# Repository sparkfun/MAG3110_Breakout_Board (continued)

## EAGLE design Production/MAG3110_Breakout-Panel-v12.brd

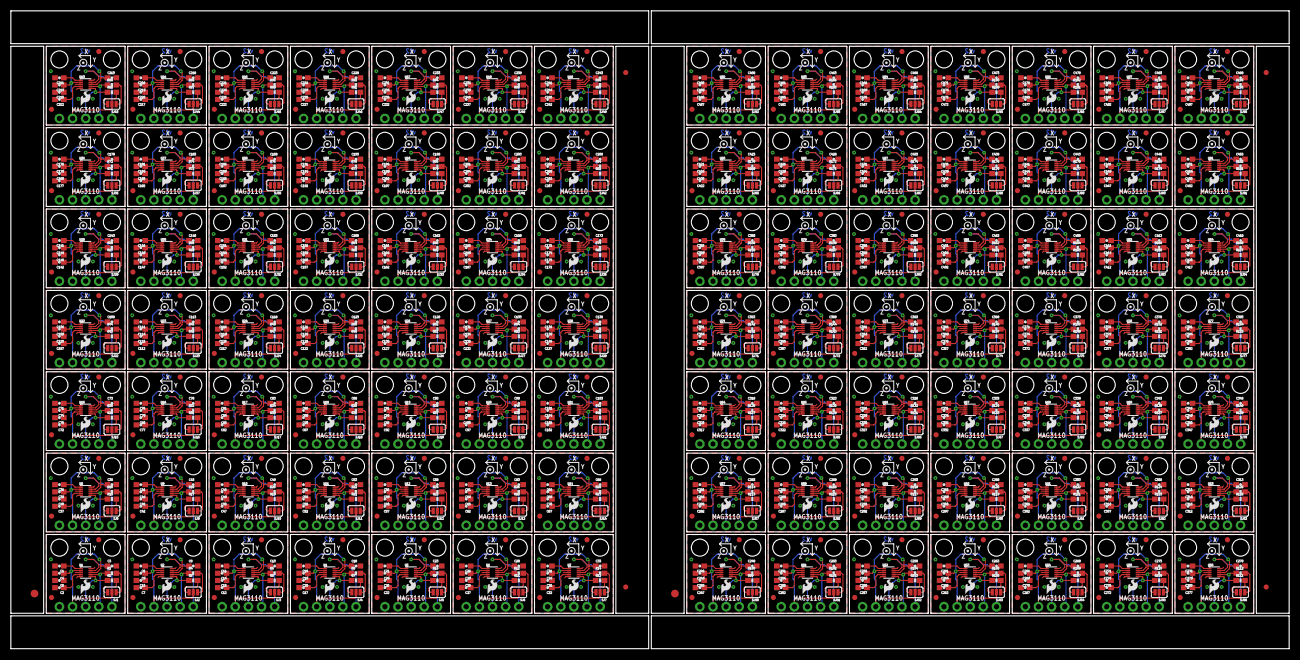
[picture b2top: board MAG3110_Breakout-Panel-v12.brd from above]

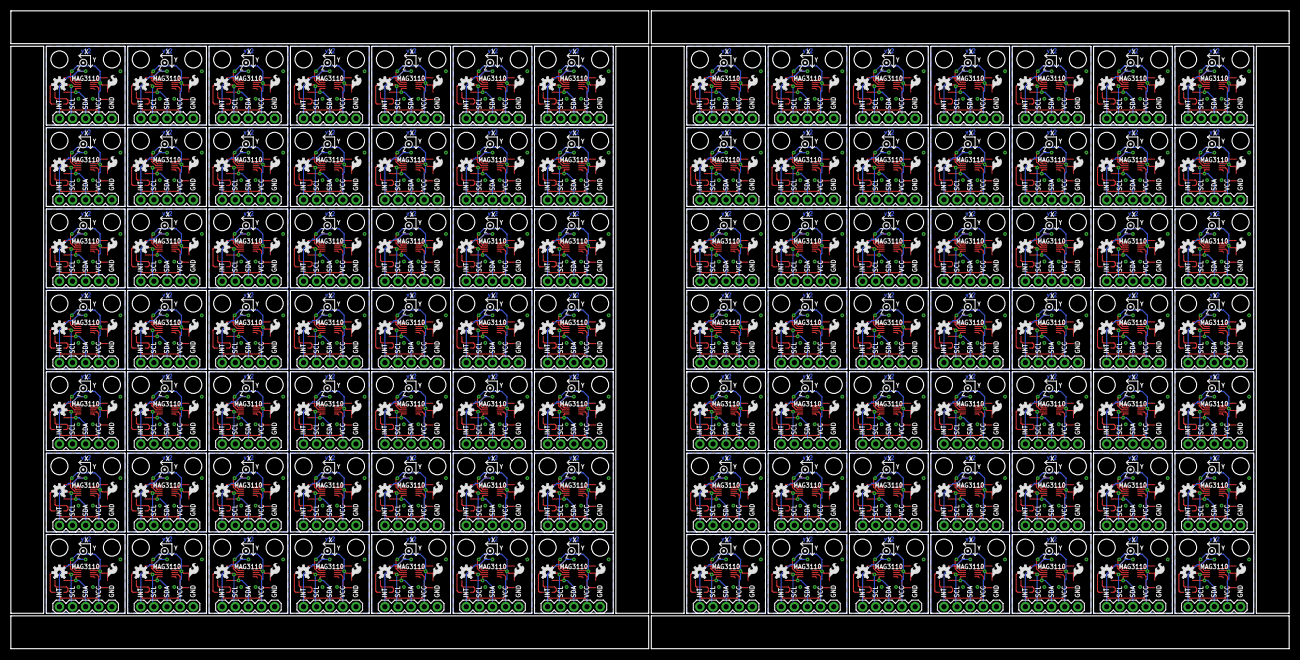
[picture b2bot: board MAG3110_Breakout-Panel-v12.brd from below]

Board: 2 copper layers, 247.4 x 123.4 mm, 1672 parts (294 on the bottom side), 882 nets.

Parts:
C1, C2, C3, C5, C6, C7, C8, C10, C11, C12, C13, C15, C16, C17, C18, C20, C21, C22, C23, C25, C26, C27, C28, C30, C31, C32, C33, C35, C36, C37, C38, C40, C41, C42, C43, C45, C46, C47, C48, C50, C51, C52, C53, C55, C56, C57, C58, C60, C61, C62, C63, C65, C66, C67, C68, C70, C71, C72, C73, C75, C76, C77, C78, C80, C81, C82, C83, C85, C86, C87, C88, C90, C91, C92, C93, C95, C96, C97, C98, C100, C101, C102, C103, C105, C106, C107, C108, C110, C111, C112, C113, C115, C116, C117, C118, C120, C121, C122, C123, C125, C126, C127, C128, C130, C131, C132, C133, C135, C136, C137, C138, C140, C141, C142, C143, C145, C146, C147, C148, C150, C151, C152, C153, C155, C156, C157, C158, C160, C161, C162, C163, C165, C166, C167, C168, C170, C171, C172, C173, C175, C176, C177, C178, C180, C181, C182, C183, C185, C186, C187, C188, C190, C191, C192, C193, C195, C196, C197, C198, C200, C201, C202, C203, C205, C206, C207, C208, C210, C211, C212, C213, C215, C216, C217, C218, C220, C221, C222, C223, C225, C226, C227, C228, C230, C231, C232, C233, C235, C236, C237, C238, C240, C241, C242, C243, C245, C246, C247, C248, C250, C251, C252, C253, C255, C256, C257, C258, C260, C261, C262, C263, C265, C266, C267, C268, C270, C271, C272, C273, C275, C276, C277, C278, C280, C281, C282, C283, C285, C286, C287, C288, C290, C291, C292, C293, C295, C296, C297, C298, C300, C301, C302, C303, C305, C306, C307, C308, C310, C311, C312, C313, C315, C316, C317, C318, C320, C321, C322, C323, C325, C326, C327, C328, C330, C331, C332, C333, C335, C336, C337, C338, C340, C341, C342, C343, C345, C346, C347, C348, C350, C351, C352, C353, C355, C356, C357, C358, C360, C361, C362, C363, C365, C366, C367, C368, C370, C371, C372, C373, C375, C376, C377, C378, C380, C381, C382, C383, C385, C386, C387, C388, C390, C391, C392, C393, C395, C396, C397, C398, C400, C401, C402, C403, C405, C406, C407, C408, C410, C411, C412, C413, C415, C416, C417, C418, C420, C421, C422, C423, C425, C426, C427, C428, C430, C431, C432, C433, C435, C436, C437, C438, C440, C441, C442, C443, C445, C446, C447, C448, C450, C451, C452, C453, C455, C456, C457, C458, C460, C461, C462, C463, C465, C466, C467, C468, C470, C471, C472, C473, C475, C476, C477, C478, C480, C481, C482, C483, C485, C486, C487, C488, C490: 0.1uF; 0603-CAP
C4, C9, C14, C19, C24, C29, C34, C39, C44, C49, C54, C59, C64, C69, C74, C79, C84, C89, C94, C99, C104, C109, C114, C119, C124, C129, C134, C139, C144, C149, C154, C159, C164, C169, C174, C179, C184, C189, C194, C199, C204, C209, C214, C219, C224, C229, C234, C239, C244, C249, C254, C259, C264, C269, C274, C279, C284, C289, C294, C299, C304, C309, C314, C319, C324, C329, C334, C339, C344, C349, C354, C359, C364, C369, C374, C379, C384, C389, C394, C399, C404, C409, C414, C419, C424, C429, C434, C439, C444, C449, C454, C459, C464, C469, C474, C479, C484, C489: 1uF; 0603-CAP
E$1, E$5: FIDUCIAL-1.5X3
E$2, E$3, E$4, E$6: FIDUCIAL-1X2
FID1, FID2, FID3, FID4, FID5, FID6, FID7, FID8, FID9, FID10, FID11, FID12, FID13, FID14, FID15, FID16, FID17, FID18, FID19, FID20, FID21, FID22, FID23, FID24, FID25, FID26, FID27, FID28, FID29, FID30, FID31, FID32, FID33, FID34, FID35, FID36, FID37, FID38, FID39, FID40, FID41, FID42, FID43, FID44, FID45, FID46, FID47, FID48, FID49, FID50, FID51, FID52, FID53, FID54, FID55, FID56, FID57, FID58, FID59, FID60, FID61, FID62, FID63, FID64, FID65, FID66, FID67, FID68, FID69, FID70, FID71, FID72, FID73, FID74, FID75, FID76, FID77, FID78, FID79, FID80, FID81, FID82, FID83, FID84, FID85, FID86, FID87, FID88, FID89, FID90, FID91, FID92, FID93, FID94, FID95, FID96, FID97, FID98, FID99, FID100, FID101, FID102, FID103, FID104, FID105, FID106, FID107, FID108, FID109, FID110, FID111, FID112, FID113, FID114, FID115, FID116, FID117, FID118, FID119, FID120, FID121, FID122, FID123, FID124, FID125, FID126, FID127, FID128, FID129, FID130, FID131, FID132, FID133, FID134, FID135, FID136, FID137, FID138, FID139, FID140, FID141, FID142, FID143, FID144, FID145, FID146, FID147, FID148, FID149, FID150, FID151, FID152, FID153, FID154, FID155, FID156, FID157, FID158, FID159, FID160, FID161, FID162, FID163, FID164, FID165, FID166, FID167, FID168, FID169, FID170, FID171, FID172, FID173, FID174, FID175, FID176, FID177, FID178, FID179, FID180, FID181, FID182, FID183, FID184, FID185, FID186, FID187, FID188, FID189, FID190, FID191, FID192, FID193, FID194, FID195, FID196: FIDUCIAL1X2; FIDUCIAL-1X2
JP1, JP5, JP11, JP16, JP21, JP26, JP31, JP36, JP41, JP46, JP51, JP56, JP61, JP66, JP71, JP76, JP81, JP86, JP91, JP96, JP101, JP106, JP111, JP116, JP121, JP126, JP131, JP136, JP141, JP146, JP151, JP156, JP161, JP166, JP171, JP176, JP181, JP186, JP191, JP196, JP201, JP206, JP211, JP216, JP221, JP226, JP231, JP236, JP241, JP246, JP251, JP256, JP261, JP266, JP271, JP276, JP281, JP286, JP291, JP296, JP301, JP306, JP311, JP316, JP321, JP326, JP331, JP336, JP341, JP346, JP351, JP356, JP361, JP366, JP371, JP376, JP381, JP386, JP391, JP396, JP401, JP406, JP411, JP416, JP421, JP426, JP431, JP436, JP441, JP446, JP451, JP456, JP461, JP466, JP471, JP476, JP481, JP486: breakout; 1X05
JP2, JP3, JP6, JP8, JP12, JP13, JP17, JP18, JP22, JP23, JP27, JP28, JP32, JP33, JP37, JP38, JP42, JP43, JP47, JP48, JP52, JP53, JP57, JP58, JP62, JP63, JP67, JP68, JP72, JP73, JP77, JP78, JP82, JP83, JP87, JP88, JP92, JP93, JP97, JP98, JP102, JP103, JP107, JP108, JP112, JP113, JP117, JP118, JP122, JP123, JP127, JP128, JP132, JP133, JP137, JP138, JP142, JP143, JP147, JP148, JP152, JP153, JP157, JP158, JP162, JP163, JP167, JP168, JP172, JP173, JP177, JP178, JP182, JP183, JP187, JP188, JP192, JP193, JP197, JP198, JP202, JP203, JP207, JP208, JP212, JP213, JP217, JP218, JP222, JP223, JP227, JP228, JP232, JP233, JP237, JP238, JP242, JP243, JP247, JP248, JP252, JP253, JP257, JP258, JP262, JP263, JP267, JP268, JP272, JP273, JP277, JP278, JP282, JP283, JP287, JP288, JP292, JP293, JP297, JP298, JP302, JP303, JP307, JP308, JP312, JP313, JP317, JP318, JP322, JP323, JP327, JP328, JP332, JP333, JP337, JP338, JP342, JP343, JP347, JP348, JP352, JP353, JP357, JP358, JP362, JP363, JP367, JP368, JP372, JP373, JP377, JP378, JP382, JP383, JP387, JP388, JP392, JP393, JP397, JP398, JP402, JP403, JP407, JP408, JP412, JP413, JP417, JP418, JP422, JP423, JP427, JP428, JP432, JP433, JP437, JP438, JP442, JP443, JP447, JP448, JP452, JP453, JP457, JP458, JP462, JP463, JP467, JP468, JP472, JP473, JP477, JP478, JP482, JP483, JP487, JP488: STAND-OFF
JP4, JP7, JP9, JP10, JP14, JP15, JP19, JP20, JP24, JP25, JP29, JP30, JP34, JP35, JP39, JP40, JP44, JP45, JP49, JP50, JP54, JP55, JP59, JP60, JP64, JP65, JP69, JP70, JP74, JP75, JP79, JP80, JP84, JP85, JP89, JP90, JP94, JP95, JP99, JP100, JP104, JP105, JP109, JP110, JP114, JP115, JP119, JP120, JP124, JP125, JP129, JP130, JP134, JP135, JP139, JP140, JP144, JP145, JP149, JP150, JP154, JP155, JP159, JP160, JP164, JP165, JP169, JP170, JP174, JP175, JP179, JP180, JP184, JP185, JP189, JP190, JP194, JP195, JP199, JP200, JP204, JP205, JP209, JP210, JP214, JP215, JP219, JP220, JP224, JP225, JP229, JP230, JP234, JP235, JP239, JP240, JP244, JP245, JP249, JP250, JP254, JP255, JP259, JP260, JP264, JP265, JP269, JP270, JP274, JP275, JP279, JP280, JP284, JP285, JP289, JP290, JP294, JP295, JP299, JP300, JP304, JP305, JP309, JP310, JP314, JP315, JP319, JP320, JP324, JP325, JP329, JP330, JP334, JP335, JP339, JP340, JP344, JP345, JP349, JP350, JP354, JP355, JP359, JP360, JP364, JP365, JP369, JP370, JP374, JP375, JP379, JP380, JP384, JP385, JP389, JP390, JP394, JP395, JP399, JP400, JP404, JP405, JP409, JP410, JP414, JP415, JP419, JP420, JP424, JP425, JP429, JP430, JP434, JP435, JP439, JP440, JP444, JP445, JP449, JP450, JP454, JP455, JP459, JP460, JP464, JP465, JP469, JP470, JP474, JP475, JP479, JP480, JP484, JP485, JP489, JP490: LOGO-SFESK; SFE-LOGO-FLAME
LOGO1, LOGO2, LOGO3, LOGO4, LOGO5, LOGO6, LOGO7, LOGO8, LOGO9, LOGO10, LOGO11, LOGO12, LOGO13, LOGO14, LOGO15, LOGO16, LOGO17, LOGO18, LOGO19, LOGO20, LOGO21, LOGO22, LOGO23, LOGO24, LOGO25, LOGO26, LOGO27, LOGO28, LOGO29, LOGO30, LOGO31, LOGO32, LOGO33, LOGO34, LOGO35, LOGO36, LOGO37, LOGO38, LOGO39, LOGO40, LOGO41, LOGO42, LOGO43, LOGO44, LOGO45, LOGO46, LOGO47, LOGO48, LOGO49, LOGO50, LOGO51, LOGO52, LOGO53, LOGO54, LOGO55, LOGO56, LOGO57, LOGO58, LOGO59, LOGO60, LOGO61, LOGO62, LOGO63, LOGO64, LOGO65, LOGO66, LOGO67, LOGO68, LOGO69, LOGO70, LOGO71, LOGO72, LOGO73, LOGO74, LOGO75, LOGO76, LOGO77, LOGO78, LOGO79, LOGO80, LOGO81, LOGO82, LOGO83, LOGO84, LOGO85, LOGO86, LOGO87, LOGO88, LOGO89, LOGO90, LOGO91, LOGO92, LOGO93, LOGO94, LOGO95, LOGO96, LOGO97, LOGO98: OSHW-LOGOS; OSHW-LOGO-S
R1, R2, R3, R4, R5, R6, R7, R8, R9, R10, R11, R12, R13, R14, R15, R16, R17, R18, R19, R20, R21, R22, R23, R24, R25, R26, R27, R28, R29, R30, R31, R32, R33, R34, R35, R36, R37, R38, R39, R40, R41, R42, R43, R44, R45, R46, R47, R48, R49, R50, R51, R52, R53, R54, R55, R56, R57, R58, R59, R60, R61, R62, R63, R64, R65, R66, R67, R68, R69, R70, R71, R72, R73, R74, R75, R76, R77, R78, R79, R80, R81, R82, R83, R84, R85, R86, R87, R88, R89, R90, R91, R92, R93, R94, R95, R96, R97, R98, R99, R100, R101, R102, R103, R104, R105, R106, R107, R108, R109, R110, R111, R112, R113, R114, R115, R116, R117, R118, R119, R120, R121, R122, R123, R124, R125, R126, R127, R128, R129, R130, R131, R132, R133, R134, R135, R136, R137, R138, R139, R140, R141, R142, R143, R144, R145, R146, R147, R148, R149, R150, R151, R152, R153, R154, R155, R156, R157, R158, R159, R160, R161, R162, R163, R164, R165, R166, R167, R168, R169, R170, R171, R172, R173, R174, R175, R176, R177, R178, R179, R180, R181, R182, R183, R184, R185, R186, R187, R188, R189, R190, R191, R192, R193, R194, R195, R196: 4.7k; 0603-RES
SJ1, SJ2, SJ3, SJ4, SJ5, SJ6, SJ7, SJ8, SJ9, SJ10, SJ11, SJ12, SJ13, SJ14, SJ15, SJ16, SJ17, SJ18, SJ19, SJ20, SJ21, SJ22, SJ23, SJ24, SJ25, SJ26, SJ27, SJ28, SJ29, SJ30, SJ31, SJ32, SJ33, SJ34, SJ35, SJ36, SJ37, SJ38, SJ39, SJ40, SJ41, SJ42, SJ43, SJ44, SJ45, SJ46, SJ47, SJ48, SJ49, SJ50, SJ51, SJ52, SJ53, SJ54, SJ55, SJ56, SJ57, SJ58, SJ59, SJ60, SJ61, SJ62, SJ63, SJ64, SJ65, SJ66, SJ67, SJ68, SJ69, SJ70, SJ71, SJ72, SJ73, SJ74, SJ75, SJ76, SJ77, SJ78, SJ79, SJ80, SJ81, SJ82, SJ83, SJ84, SJ85, SJ86, SJ87, SJ88, SJ89, SJ90, SJ91, SJ92, SJ93, SJ94, SJ95, SJ96, SJ97, SJ98: SJ_3_PASTE1&2&3
U1, U2, U3, U4, U5, U6, U7, U8, U9, U10, U11, U12, U13, U14, U15, U16, U17, U18, U19, U20, U21, U22, U23, U24, U25, U26, U27, U28, U29, U30, U31, U32, U33, U34, U35, U36, U37, U38, U39, U40, U41, U42, U43, U44, U45, U46, U47, U48, U49, U50, U51, U52, U53, U54, U55, U56, U57, U58, U59, U60, U61, U62, U63, U64, U65, U66, U67, U68, U69, U70, U71, U72, U73, U74, U75, U76, U77, U78, U79, U80, U81, U82, U83, U84, U85, U86, U87, U88, U89, U90, U91, U92, U93, U94, U95, U96, U97, U98: MAG31101:1; DFN-10-W

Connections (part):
GND: C1.2, C2.2, C3.2, C4.2, C5.2, JP1.1, U1.5, U1.10
GND1: C6.2, C7.2, C8.2, C9.2, C10.2, JP5.1, U2.5, U2.10
GND2: C11.2, C12.2, C13.2, C14.2, C15.2, JP11.1, U3.5, U3.10
GND3: C16.2, C17.2, C18.2, C19.2, C20.2, JP16.1, U4.5, U4.10
GND4: C21.2, C22.2, C23.2, C24.2, C25.2, JP21.1, U5.5, U5.10
GND5: C26.2, C27.2, C28.2, C29.2, C30.2, JP26.1, U6.5, U6.10
GND6: C31.2, C32.2, C33.2, C34.2, C35.2, JP31.1, U7.5, U7.10
GND7: C36.2, C37.2, C38.2, C39.2, C40.2, JP36.1, U8.5, U8.10
GND8: C41.2, C42.2, C43.2, C44.2, C45.2, JP41.1, U9.5, U9.10
GND9: C46.2, C47.2, C48.2, C49.2, C50.2, JP46.1, U10.5, U10.10
GND10: C51.2, C52.2, C53.2, C54.2, C55.2, JP51.1, U11.5, U11.10
GND11: C56.2, C57.2, C58.2, C59.2, C60.2, JP56.1, U12.5, U12.10
GND12: C61.2, C62.2, C63.2, C64.2, C65.2, JP61.1, U13.5, U13.10
GND13: C66.2, C67.2, C68.2, C69.2, C70.2, JP66.1, U14.5, U14.10
GND14: C71.2, C72.2, C73.2, C74.2, C75.2, JP71.1, U15.5, U15.10
GND15: C76.2, C77.2, C78.2, C79.2, C80.2, JP76.1, U16.5, U16.10
GND16: C81.2, C82.2, C83.2, C84.2, C85.2, JP81.1, U17.5, U17.10
GND17: C86.2, C87.2, C88.2, C89.2, C90.2, JP86.1, U18.5, U18.10
GND18: C91.2, C92.2, C93.2, C94.2, C95.2, JP91.1, U19.5, U19.10
GND19: C96.2, C97.2, C98.2, C99.2, C100.2, JP96.1, U20.5, U20.10
GND20: C101.2, C102.2, C103.2, C104.2, C105.2, JP101.1, U21.5, U21.10
GND21: C106.2, C107.2, C108.2, C109.2, C110.2, JP106.1, U22.5, U22.10
GND22: C111.2, C112.2, C113.2, C114.2, C115.2, JP111.1, U23.5, U23.10
GND23: C116.2, C117.2, C118.2, C119.2, C120.2, JP116.1, U24.5, U24.10
GND24: C121.2, C122.2, C123.2, C124.2, C125.2, JP121.1, U25.5, U25.10
GND25: C126.2, C127.2, C128.2, C129.2, C130.2, JP126.1, U26.5, U26.10
GND26: C131.2, C132.2, C133.2, C134.2, C135.2, JP131.1, U27.5, U27.10
GND27: C136.2, C137.2, C138.2, C139.2, C140.2, JP136.1, U28.5, U28.10
GND28: C141.2, C142.2, C143.2, C144.2, C145.2, JP141.1, U29.5, U29.10
GND29: C146.2, C147.2, C148.2, C149.2, C150.2, JP146.1, U30.5, U30.10
GND30: C151.2, C152.2, C153.2, C154.2, C155.2, JP151.1, U31.5, U31.10
GND31: C156.2, C157.2, C158.2, C159.2, C160.2, JP156.1, U32.5, U32.10
GND32: C161.2, C162.2, C163.2, C164.2, C165.2, JP161.1, U33.5, U33.10
GND33: C166.2, C167.2, C168.2, C169.2, C170.2, JP166.1, U34.5, U34.10
GND34: C171.2, C172.2, C173.2, C174.2, C175.2, JP171.1, U35.5, U35.10
GND35: C176.2, C177.2, C178.2, C179.2, C180.2, JP176.1, U36.5, U36.10
GND36: C181.2, C182.2, C183.2, C184.2, C185.2, JP181.1, U37.5, U37.10
GND37: C186.2, C187.2, C188.2, C189.2, C190.2, JP186.1, U38.5, U38.10
GND38: C191.2, C192.2, C193.2, C194.2, C195.2, JP191.1, U39.5, U39.10
GND39: C196.2, C197.2, C198.2, C199.2, C200.2, JP196.1, U40.5, U40.10
GND40: C201.2, C202.2, C203.2, C204.2, C205.2, JP201.1, U41.5, U41.10
GND41: C206.2, C207.2, C208.2, C209.2, C210.2, JP206.1, U42.5, U42.10
GND42: C211.2, C212.2, C213.2, C214.2, C215.2, JP211.1, U43.5, U43.10
GND43: C216.2, C217.2, C218.2, C219.2, C220.2, JP216.1, U44.5, U44.10
GND44: C221.2, C222.2, C223.2, C224.2, C225.2, JP221.1, U45.5, U45.10
GND45: C226.2, C227.2, C228.2, C229.2, C230.2, JP226.1, U46.5, U46.10
GND46: C231.2, C232.2, C233.2, C234.2, C235.2, JP231.1, U47.5, U47.10
GND47: C236.2, C237.2, C238.2, C239.2, C240.2, JP236.1, U48.5, U48.10
GND48: C241.2, C242.2, C243.2, C244.2, C245.2, JP241.1, U49.5, U49.10
GND49: C246.2, C247.2, C248.2, C249.2, C250.2, JP246.1, U50.5, U50.10
GND50: C251.2, C252.2, C253.2, C254.2, C255.2, JP251.1, U51.5, U51.10
GND51: C256.2, C257.2, C258.2, C259.2, C260.2, JP256.1, U52.5, U52.10
GND52: C261.2, C262.2, C263.2, C264.2, C265.2, JP261.1, U53.5, U53.10
GND53: C266.2, C267.2, C268.2, C269.2, C270.2, JP266.1, U54.5, U54.10
GND54: C271.2, C272.2, C273.2, C274.2, C275.2, JP271.1, U55.5, U55.10
GND55: C276.2, C277.2, C278.2, C279.2, C280.2, JP276.1, U56.5, U56.10
GND56: C281.2, C282.2, C283.2, C284.2, C285.2, JP281.1, U57.5, U57.10
GND57: C286.2, C287.2, C288.2, C289.2, C290.2, JP286.1, U58.5, U58.10
GND58: C291.2, C292.2, C293.2, C294.2, C295.2, JP291.1, U59.5, U59.10
GND59: C296.2, C297.2, C298.2, C299.2, C300.2, JP296.1, U60.5, U60.10
GND60: C301.2, C302.2, C303.2, C304.2, C305.2, JP301.1, U61.5, U61.10
GND61: C306.2, C307.2, C308.2, C309.2, C310.2, JP306.1, U62.5, U62.10
GND62: C311.2, C312.2, C313.2, C314.2, C315.2, JP311.1, U63.5, U63.10
GND63: C316.2, C317.2, C318.2, C319.2, C320.2, JP316.1, U64.5, U64.10
GND64: C321.2, C322.2, C323.2, C324.2, C325.2, JP321.1, U65.5, U65.10
GND65: C326.2, C327.2, C328.2, C329.2, C330.2, JP326.1, U66.5, U66.10
GND66: C331.2, C332.2, C333.2, C334.2, C335.2, JP331.1, U67.5, U67.10
GND67: C336.2, C337.2, C338.2, C339.2, C340.2, JP336.1, U68.5, U68.10
GND68: C341.2, C342.2, C343.2, C344.2, C345.2, JP341.1, U69.5, U69.10
GND69: C346.2, C347.2, C348.2, C349.2, C350.2, JP346.1, U70.5, U70.10
GND70: C351.2, C352.2, C353.2, C354.2, C355.2, JP351.1, U71.5, U71.10
GND71: C356.2, C357.2, C358.2, C359.2, C360.2, JP356.1, U72.5, U72.10
GND72: C361.2, C362.2, C363.2, C364.2, C365.2, JP361.1, U73.5, U73.10
GND73: C366.2, C367.2, C368.2, C369.2, C370.2, JP366.1, U74.5, U74.10
GND74: C371.2, C372.2, C373.2, C374.2, C375.2, JP371.1, U75.5, U75.10
GND75: C376.2, C377.2, C378.2, C379.2, C380.2, JP376.1, U76.5, U76.10
GND76: C381.2, C382.2, C383.2, C384.2, C385.2, JP381.1, U77.5, U77.10
GND77: C386.2, C387.2, C388.2, C389.2, C390.2, JP386.1, U78.5, U78.10
GND78: C391.2, C392.2, C393.2, C394.2, C395.2, JP391.1, U79.5, U79.10
GND79: C396.2, C397.2, C398.2, C399.2, C400.2, JP396.1, U80.5, U80.10
GND80: C401.2, C402.2, C403.2, C404.2, C405.2, JP401.1, U81.5, U81.10
GND81: C406.2, C407.2, C408.2, C409.2, C410.2, JP406.1, U82.5, U82.10
GND82: C411.2, C412.2, C413.2, C414.2, C415.2, JP411.1, U83.5, U83.10
GND83: C416.2, C417.2, C418.2, C419.2, C420.2, JP416.1, U84.5, U84.10
GND84: C421.2, C422.2, C423.2, C424.2, C425.2, JP421.1, U85.5, U85.10
GND85: C426.2, C427.2, C428.2, C429.2, C430.2, JP426.1, U86.5, U86.10
GND86: C431.2, C432.2, C433.2, C434.2, C435.2, JP431.1, U87.5, U87.10
GND87: C436.2, C437.2, C438.2, C439.2, C440.2, JP436.1, U88.5, U88.10
GND88: C441.2, C442.2, C443.2, C444.2, C445.2, JP441.1, U89.5, U89.10
GND89: C446.2, C447.2, C448.2, C449.2, C450.2, JP446.1, U90.5, U90.10
GND90: C451.2, C452.2, C453.2, C454.2, C455.2, JP451.1, U91.5, U91.10
GND91: C456.2, C457.2, C458.2, C459.2, C460.2, JP456.1, U92.5, U92.10
GND92: C461.2, C462.2, C463.2, C464.2, C465.2, JP461.1, U93.5, U93.10
GND93: C466.2, C467.2, C468.2, C469.2, C470.2, JP466.1, U94.5, U94.10
GND94: C471.2, C472.2, C473.2, C474.2, C475.2, JP471.1, U95.5, U95.10
GND95: C476.2, C477.2, C478.2, C479.2, C480.2, JP476.1, U96.5, U96.10
GND96: C481.2, C482.2, C483.2, C484.2, C485.2, JP481.1, U97.5, U97.10
GND97: C486.2, C487.2, C488.2, C489.2, C490.2, JP486.1, U98.5, U98.10
INT: JP1.5, U1.9
INT1: JP5.5, U2.9
INT2: JP11.5, U3.9
INT3: JP16.5, U4.9
INT4: JP21.5, U5.9
INT5: JP26.5, U6.9
INT6: JP31.5, U7.9
INT7: JP36.5, U8.9
INT8: JP41.5, U9.9
INT9: JP46.5, U10.9
INT10: JP51.5, U11.9
INT11: JP56.5, U12.9
INT12: JP61.5, U13.9
INT13: JP66.5, U14.9
INT14: JP71.5, U15.9
INT15: JP76.5, U16.9
INT16: JP81.5, U17.9
INT17: JP86.5, U18.9
INT18: JP91.5, U19.9
INT19: JP96.5, U20.9
INT20: JP101.5, U21.9
INT21: JP106.5, U22.9
INT22: JP111.5, U23.9
INT23: JP116.5, U24.9
INT24: JP121.5, U25.9
INT25: JP126.5, U26.9
INT26: JP131.5, U27.9
INT27: JP136.5, U28.9
INT28: JP141.5, U29.9
INT29: JP146.5, U30.9
INT30: JP151.5, U31.9
INT31: JP156.5, U32.9
INT32: JP161.5, U33.9
INT33: JP166.5, U34.9
INT34: JP171.5, U35.9
INT35: JP176.5, U36.9
INT36: JP181.5, U37.9
INT37: JP186.5, U38.9
INT38: JP191.5, U39.9
INT39: JP196.5, U40.9
INT40: JP201.5, U41.9
INT41: JP206.5, U42.9
INT42: JP211.5, U43.9
INT43: JP216.5, U44.9
INT44: JP221.5, U45.9
INT45: JP226.5, U46.9
INT46: JP231.5, U47.9
INT47: JP236.5, U48.9
INT48: JP241.5, U49.9
INT49: JP246.5, U50.9
INT50: JP251.5, U51.9
INT51: JP256.5, U52.9
INT52: JP261.5, U53.9
INT53: JP266.5, U54.9
INT54: JP271.5, U55.9
INT55: JP276.5, U56.9
INT56: JP281.5, U57.9
INT57: JP286.5, U58.9
INT58: JP291.5, U59.9
INT59: JP296.5, U60.9
INT60: JP301.5, U61.9
INT61: JP306.5, U62.9
INT62: JP311.5, U63.9
INT63: JP316.5, U64.9
INT64: JP321.5, U65.9
INT65: JP326.5, U66.9
INT66: JP331.5, U67.9
INT67: JP336.5, U68.9
INT68: JP341.5, U69.9
INT69: JP346.5, U70.9
INT70: JP351.5, U71.9
INT71: JP356.5, U72.9
INT72: JP361.5, U73.9
INT73: JP366.5, U74.9
INT74: JP371.5, U75.9
INT75: JP376.5, U76.9
INT76: JP381.5, U77.9
INT77: JP386.5, U78.9
INT78: JP391.5, U79.9
INT79: JP396.5, U80.9
INT80: JP401.5, U81.9
INT81: JP406.5, U82.9
INT82: JP411.5, U83.9
INT83: JP416.5, U84.9
INT84: JP421.5, U85.9
INT85: JP426.5, U86.9
INT86: JP431.5, U87.9
INT87: JP436.5, U88.9
INT88: JP441.5, U89.9
INT89: JP446.5, U90.9
INT90: JP451.5, U91.9
INT91: JP456.5, U92.9
INT92: JP461.5, U93.9
INT93: JP466.5, U94.9
INT94: JP471.5, U95.9
INT95: JP476.5, U96.9
INT96: JP481.5, U97.9
INT97: JP486.5, U98.9
unnamed: C2.1, U1.4
unnamed: C1.1, U1.1
unnamed: R2.2, SJ1.1
unnamed: R1.2, SJ1.3
unnamed: C7.1, U2.4
unnamed: C6.1, U2.1
unnamed: R4.2, SJ2.1
unnamed: R3.2, SJ2.3
unnamed: C12.1, U3.4
unnamed: C11.1, U3.1
unnamed: R6.2, SJ3.1
unnamed: R5.2, SJ3.3
unnamed: C17.1, U4.4
unnamed: C16.1, U4.1
unnamed: R8.2, SJ4.1
unnamed: R7.2, SJ4.3
unnamed: C22.1, U5.4
unnamed: C21.1, U5.1
unnamed: R10.2, SJ5.1
unnamed: R9.2, SJ5.3
unnamed: C27.1, U6.4
unnamed: C26.1, U6.1
unnamed: R12.2, SJ6.1
unnamed: R11.2, SJ6.3
unnamed: C32.1, U7.4
unnamed: C31.1, U7.1
unnamed: R14.2, SJ7.1
unnamed: R13.2, SJ7.3
unnamed: C37.1, U8.4
unnamed: C36.1, U8.1
unnamed: R16.2, SJ8.1
unnamed: R15.2, SJ8.3
unnamed: C42.1, U9.4
unnamed: C41.1, U9.1
unnamed: R18.2, SJ9.1
unnamed: R17.2, SJ9.3
unnamed: C47.1, U10.4
unnamed: C46.1, U10.1
unnamed: R20.2, SJ10.1
unnamed: R19.2, SJ10.3
unnamed: C52.1, U11.4
unnamed: C51.1, U11.1
unnamed: R22.2, SJ11.1
unnamed: R21.2, SJ11.3
unnamed: C57.1, U12.4
unnamed: C56.1, U12.1
unnamed: R24.2, SJ12.1
unnamed: R23.2, SJ12.3
unnamed: C62.1, U13.4
unnamed: C61.1, U13.1
unnamed: R26.2, SJ13.1
unnamed: R25.2, SJ13.3
unnamed: C67.1, U14.4
unnamed: C66.1, U14.1
unnamed: R28.2, SJ14.1
unnamed: R27.2, SJ14.3
unnamed: C72.1, U15.4
unnamed: C71.1, U15.1
unnamed: R30.2, SJ15.1
unnamed: R29.2, SJ15.3
unnamed: C77.1, U16.4
unnamed: C76.1, U16.1
unnamed: R32.2, SJ16.1
unnamed: R31.2, SJ16.3
unnamed: C82.1, U17.4
unnamed: C81.1, U17.1
unnamed: R34.2, SJ17.1
unnamed: R33.2, SJ17.3
unnamed: C87.1, U18.4
unnamed: C86.1, U18.1
unnamed: R36.2, SJ18.1
unnamed: R35.2, SJ18.3
unnamed: C92.1, U19.4
unnamed: C91.1, U19.1
unnamed: R38.2, SJ19.1
unnamed: R37.2, SJ19.3
unnamed: C97.1, U20.4
unnamed: C96.1, U20.1
unnamed: R40.2, SJ20.1
unnamed: R39.2, SJ20.3
unnamed: C102.1, U21.4
unnamed: C101.1, U21.1
unnamed: R42.2, SJ21.1
unnamed: R41.2, SJ21.3
unnamed: C107.1, U22.4
unnamed: C106.1, U22.1
unnamed: R44.2, SJ22.1
unnamed: R43.2, SJ22.3
unnamed: C112.1, U23.4
unnamed: C111.1, U23.1
unnamed: R46.2, SJ23.1
unnamed: R45.2, SJ23.3
unnamed: C117.1, U24.4
unnamed: C116.1, U24.1
unnamed: R48.2, SJ24.1
unnamed: R47.2, SJ24.3
unnamed: C122.1, U25.4
unnamed: C121.1, U25.1
unnamed: R50.2, SJ25.1
unnamed: R49.2, SJ25.3
unnamed: C127.1, U26.4
unnamed: C126.1, U26.1
unnamed: R52.2, SJ26.1
unnamed: R51.2, SJ26.3
unnamed: C132.1, U27.4
unnamed: C131.1, U27.1
unnamed: R54.2, SJ27.1
unnamed: R53.2, SJ27.3
unnamed: C137.1, U28.4
unnamed: C136.1, U28.1
unnamed: R56.2, SJ28.1
unnamed: R55.2, SJ28.3
unnamed: C142.1, U29.4
unnamed: C141.1, U29.1
unnamed: R58.2, SJ29.1
unnamed: R57.2, SJ29.3
unnamed: C147.1, U30.4
unnamed: C146.1, U30.1
unnamed: R60.2, SJ30.1
unnamed: R59.2, SJ30.3
unnamed: C152.1, U31.4
unnamed: C151.1, U31.1
unnamed: R62.2, SJ31.1
unnamed: R61.2, SJ31.3
unnamed: C157.1, U32.4
unnamed: C156.1, U32.1
unnamed: R64.2, SJ32.1
unnamed: R63.2, SJ32.3
unnamed: C162.1, U33.4
unnamed: C161.1, U33.1
unnamed: R66.2, SJ33.1
unnamed: R65.2, SJ33.3
unnamed: C167.1, U34.4
unnamed: C166.1, U34.1
unnamed: R68.2, SJ34.1
unnamed: R67.2, SJ34.3
unnamed: C172.1, U35.4
unnamed: C171.1, U35.1
unnamed: R70.2, SJ35.1
unnamed: R69.2, SJ35.3
unnamed: C177.1, U36.4
unnamed: C176.1, U36.1
unnamed: R72.2, SJ36.1
unnamed: R71.2, SJ36.3
unnamed: C182.1, U37.4
unnamed: C181.1, U37.1
unnamed: R74.2, SJ37.1
unnamed: R73.2, SJ37.3
unnamed: C187.1, U38.4
unnamed: C186.1, U38.1
unnamed: R76.2, SJ38.1
unnamed: R75.2, SJ38.3
unnamed: C192.1, U39.4
unnamed: C191.1, U39.1
unnamed: R78.2, SJ39.1
unnamed: R77.2, SJ39.3
unnamed: C197.1, U40.4
unnamed: C196.1, U40.1
unnamed: R80.2, SJ40.1
unnamed: R79.2, SJ40.3
unnamed: C202.1, U41.4
unnamed: C201.1, U41.1
unnamed: R82.2, SJ41.1
unnamed: R81.2, SJ41.3
unnamed: C207.1, U42.4
unnamed: C206.1, U42.1
unnamed: R84.2, SJ42.1
unnamed: R83.2, SJ42.3
unnamed: C212.1, U43.4
unnamed: C211.1, U43.1
unnamed: R86.2, SJ43.1
unnamed: R85.2, SJ43.3
unnamed: C217.1, U44.4
unnamed: C216.1, U44.1
unnamed: R88.2, SJ44.1
unnamed: R87.2, SJ44.3
unnamed: C222.1, U45.4
unnamed: C221.1, U45.1
unnamed: R90.2, SJ45.1
unnamed: R89.2, SJ45.3
unnamed: C227.1, U46.4
unnamed: C226.1, U46.1
unnamed: R92.2, SJ46.1
unnamed: R91.2, SJ46.3
unnamed: C232.1, U47.4
unnamed: C231.1, U47.1
unnamed: R94.2, SJ47.1
unnamed: R93.2, SJ47.3
unnamed: C237.1, U48.4
unnamed: C236.1, U48.1
unnamed: R96.2, SJ48.1
unnamed: R95.2, SJ48.3
unnamed: C242.1, U49.4
unnamed: C241.1, U49.1
unnamed: R98.2, SJ49.1
unnamed: R97.2, SJ49.3
unnamed: C247.1, U50.4
unnamed: C246.1, U50.1
unnamed: R100.2, SJ50.1
unnamed: R99.2, SJ50.3
unnamed: C252.1, U51.4
unnamed: C251.1, U51.1
unnamed: R102.2, SJ51.1
unnamed: R101.2, SJ51.3
unnamed: C257.1, U52.4
unnamed: C256.1, U52.1
unnamed: R104.2, SJ52.1
unnamed: R103.2, SJ52.3
unnamed: C262.1, U53.4
unnamed: C261.1, U53.1
unnamed: R106.2, SJ53.1
unnamed: R105.2, SJ53.3
unnamed: C267.1, U54.4
unnamed: C266.1, U54.1
unnamed: R108.2, SJ54.1
unnamed: R107.2, SJ54.3
unnamed: C272.1, U55.4
unnamed: C271.1, U55.1
unnamed: R110.2, SJ55.1
unnamed: R109.2, SJ55.3
unnamed: C277.1, U56.4
unnamed: C276.1, U56.1
unnamed: R112.2, SJ56.1
unnamed: R111.2, SJ56.3
unnamed: C282.1, U57.4
unnamed: C281.1, U57.1
unnamed: R114.2, SJ57.1
unnamed: R113.2, SJ57.3
unnamed: C287.1, U58.4
unnamed: C286.1, U58.1
unnamed: R116.2, SJ58.1
unnamed: R115.2, SJ58.3
unnamed: C292.1, U59.4
unnamed: C291.1, U59.1
unnamed: R118.2, SJ59.1
unnamed: R117.2, SJ59.3
unnamed: C297.1, U60.4
unnamed: C296.1, U60.1
unnamed: R120.2, SJ60.1
unnamed: R119.2, SJ60.3
unnamed: C302.1, U61.4
unnamed: C301.1, U61.1
unnamed: R122.2, SJ61.1
unnamed: R121.2, SJ61.3
unnamed: C307.1, U62.4
unnamed: C306.1, U62.1
unnamed: R124.2, SJ62.1
unnamed: R123.2, SJ62.3
unnamed: C312.1, U63.4
unnamed: C311.1, U63.1
unnamed: R126.2, SJ63.1
unnamed: R125.2, SJ63.3
unnamed: C317.1, U64.4
unnamed: C316.1, U64.1
unnamed: R128.2, SJ64.1
unnamed: R127.2, SJ64.3
unnamed: C322.1, U65.4
unnamed: C321.1, U65.1
unnamed: R130.2, SJ65.1
unnamed: R129.2, SJ65.3
unnamed: C327.1, U66.4
unnamed: C326.1, U66.1
unnamed: R132.2, SJ66.1
unnamed: R131.2, SJ66.3
unnamed: C332.1, U67.4
unnamed: C331.1, U67.1
unnamed: R134.2, SJ67.1
unnamed: R133.2, SJ67.3
unnamed: C337.1, U68.4
unnamed: C336.1, U68.1
unnamed: R136.2, SJ68.1
unnamed: R135.2, SJ68.3
unnamed: C342.1, U69.4
unnamed: C341.1, U69.1
unnamed: R138.2, SJ69.1
unnamed: R137.2, SJ69.3
unnamed: C347.1, U70.4
unnamed: C346.1, U70.1
unnamed: R140.2, SJ70.1
unnamed: R139.2, SJ70.3
unnamed: C352.1, U71.4
unnamed: C351.1, U71.1
unnamed: R142.2, SJ71.1
unnamed: R141.2, SJ71.3
unnamed: C357.1, U72.4
unnamed: C356.1, U72.1
unnamed: R144.2, SJ72.1
unnamed: R143.2, SJ72.3
unnamed: C362.1, U73.4
unnamed: C361.1, U73.1
unnamed: R146.2, SJ73.1
unnamed: R145.2, SJ73.3
unnamed: C367.1, U74.4
unnamed: C366.1, U74.1
unnamed: R148.2, SJ74.1
unnamed: R147.2, SJ74.3
unnamed: C372.1, U75.4
unnamed: C371.1, U75.1
unnamed: R150.2, SJ75.1
unnamed: R149.2, SJ75.3
unnamed: C377.1, U76.4
unnamed: C376.1, U76.1
unnamed: R152.2, SJ76.1
unnamed: R151.2, SJ76.3
unnamed: C382.1, U77.4
unnamed: C381.1, U77.1
unnamed: R154.2, SJ77.1
unnamed: R153.2, SJ77.3
unnamed: C387.1, U78.4
unnamed: C386.1, U78.1
unnamed: R156.2, SJ78.1
unnamed: R155.2, SJ78.3
unnamed: C392.1, U79.4
unnamed: C391.1, U79.1
unnamed: R158.2, SJ79.1
unnamed: R157.2, SJ79.3
unnamed: C397.1, U80.4
unnamed: C396.1, U80.1
unnamed: R160.2, SJ80.1
unnamed: R159.2, SJ80.3
unnamed: C402.1, U81.4
unnamed: C401.1, U81.1
unnamed: R162.2, SJ81.1
unnamed: R161.2, SJ81.3
unnamed: C407.1, U82.4
unnamed: C406.1, U82.1
unnamed: R164.2, SJ82.1
unnamed: R163.2, SJ82.3
unnamed: C412.1, U83.4
unnamed: C411.1, U83.1
unnamed: R166.2, SJ83.1
unnamed: R165.2, SJ83.3
unnamed: C417.1, U84.4
unnamed: C416.1, U84.1
unnamed: R168.2, SJ84.1
unnamed: R167.2, SJ84.3
unnamed: C422.1, U85.4
unnamed: C421.1, U85.1
unnamed: R170.2, SJ85.1
unnamed: R169.2, SJ85.3
unnamed: C427.1, U86.4
unnamed: C426.1, U86.1
unnamed: R172.2, SJ86.1
unnamed: R171.2, SJ86.3
unnamed: C432.1, U87.4
unnamed: C431.1, U87.1
unnamed: R174.2, SJ87.1
unnamed: R173.2, SJ87.3
unnamed: C437.1, U88.4
unnamed: C436.1, U88.1
unnamed: R176.2, SJ88.1
unnamed: R175.2, SJ88.3
unnamed: C442.1, U89.4
unnamed: C441.1, U89.1
unnamed: R178.2, SJ89.1
unnamed: R177.2, SJ89.3
unnamed: C447.1, U90.4
unnamed: C446.1, U90.1
unnamed: R180.2, SJ90.1
unnamed: R179.2, SJ90.3
unnamed: C452.1, U91.4
unnamed: C451.1, U91.1
unnamed: R182.2, SJ91.1
unnamed: R181.2, SJ91.3
unnamed: C457.1, U92.4
unnamed: C456.1, U92.1
unnamed: R184.2, SJ92.1
unnamed: R183.2, SJ92.3
unnamed: C462.1, U93.4
unnamed: C461.1, U93.1
unnamed: R186.2, SJ93.1
unnamed: R185.2, SJ93.3
unnamed: C467.1, U94.4
unnamed: C466.1, U94.1
unnamed: R188.2, SJ94.1
unnamed: R187.2, SJ94.3
unnamed: C472.1, U95.4
unnamed: C471.1, U95.1
unnamed: R190.2, SJ95.1
unnamed: R189.2, SJ95.3
unnamed: C477.1, U96.4
unnamed: C476.1, U96.1
unnamed: R192.2, SJ96.1
unnamed: R191.2, SJ96.3
unnamed: C482.1, U97.4
unnamed: C481.1, U97.1
unnamed: R194.2, SJ97.1
unnamed: R193.2, SJ97.3
unnamed: C487.1, U98.4
unnamed: C486.1, U98.1
unnamed: R196.2, SJ98.1
unnamed: R195.2, SJ98.3
SCL: JP1.4, R2.1, U1.7
SCL1: JP5.4, R4.1, U2.7
SCL2: JP11.4, R6.1, U3.7
SCL3: JP16.4, R8.1, U4.7
SCL4: JP21.4, R10.1, U5.7
SCL5: JP26.4, R12.1, U6.7
SCL6: JP31.4, R14.1, U7.7
SCL7: JP36.4, R16.1, U8.7
SCL8: JP41.4, R18.1, U9.7
SCL9: JP46.4, R20.1, U10.7
SCL10: JP51.4, R22.1, U11.7
SCL11: JP56.4, R24.1, U12.7
SCL12: JP61.4, R26.1, U13.7
SCL13: JP66.4, R28.1, U14.7
SCL14: JP71.4, R30.1, U15.7
SCL15: JP76.4, R32.1, U16.7
SCL16: JP81.4, R34.1, U17.7
SCL17: JP86.4, R36.1, U18.7
SCL18: JP91.4, R38.1, U19.7
SCL19: JP96.4, R40.1, U20.7
SCL20: JP101.4, R42.1, U21.7
SCL21: JP106.4, R44.1, U22.7
SCL22: JP111.4, R46.1, U23.7
SCL23: JP116.4, R48.1, U24.7
SCL24: JP121.4, R50.1, U25.7
SCL25: JP126.4, R52.1, U26.7
SCL26: JP131.4, R54.1, U27.7
SCL27: JP136.4, R56.1, U28.7
SCL28: JP141.4, R58.1, U29.7
SCL29: JP146.4, R60.1, U30.7
SCL30: JP151.4, R62.1, U31.7
SCL31: JP156.4, R64.1, U32.7
SCL32: JP161.4, R66.1, U33.7
SCL33: JP166.4, R68.1, U34.7
SCL34: JP171.4, R70.1, U35.7
SCL35: JP176.4, R72.1, U36.7
SCL36: JP181.4, R74.1, U37.7
SCL37: JP186.4, R76.1, U38.7
SCL38: JP191.4, R78.1, U39.7
SCL39: JP196.4, R80.1, U40.7
SCL40: JP201.4, R82.1, U41.7
SCL41: JP206.4, R84.1, U42.7
SCL42: JP211.4, R86.1, U43.7
SCL43: JP216.4, R88.1, U44.7
SCL44: JP221.4, R90.1, U45.7
SCL45: JP226.4, R92.1, U46.7
SCL46: JP231.4, R94.1, U47.7
SCL47: JP236.4, R96.1, U48.7
SCL48: JP241.4, R98.1, U49.7
SCL49: JP246.4, R100.1, U50.7
SCL50: JP251.4, R102.1, U51.7
SCL51: JP256.4, R104.1, U52.7
SCL52: JP261.4, R106.1, U53.7
SCL53: JP266.4, R108.1, U54.7
SCL54: JP271.4, R110.1, U55.7
SCL55: JP276.4, R112.1, U56.7
SCL56: JP281.4, R114.1, U57.7
SCL57: JP286.4, R116.1, U58.7
SCL58: JP291.4, R118.1, U59.7
SCL59: JP296.4, R120.1, U60.7
SCL60: JP301.4, R122.1, U61.7
SCL61: JP306.4, R124.1, U62.7
SCL62: JP311.4, R126.1, U63.7
SCL63: JP316.4, R128.1, U64.7
SCL64: JP321.4, R130.1, U65.7
SCL65: JP326.4, R132.1, U66.7
SCL66: JP331.4, R134.1, U67.7
SCL67: JP336.4, R136.1, U68.7
SCL68: JP341.4, R138.1, U69.7
SCL69: JP346.4, R140.1, U70.7
SCL70: JP351.4, R142.1, U71.7
SCL71: JP356.4, R144.1, U72.7
SCL72: JP361.4, R146.1, U73.7
SCL73: JP366.4, R148.1, U74.7
SCL74: JP371.4, R150.1, U75.7
SCL75: JP376.4, R152.1, U76.7
SCL76: JP381.4, R154.1, U77.7
SCL77: JP386.4, R156.1, U78.7
SCL78: JP391.4, R158.1, U79.7
SCL79: JP396.4, R160.1, U80.7
SCL80: JP401.4, R162.1, U81.7
SCL81: JP406.4, R164.1, U82.7
SCL82: JP411.4, R166.1, U83.7
SCL83: JP416.4, R168.1, U84.7
SCL84: JP421.4, R170.1, U85.7
SCL85: JP426.4, R172.1, U86.7
SCL86: JP431.4, R174.1, U87.7
SCL87: JP436.4, R176.1, U88.7
SCL88: JP441.4, R178.1, U89.7
SCL89: JP446.4, R180.1, U90.7
SCL90: JP451.4, R182.1, U91.7
SCL91: JP456.4, R184.1, U92.7
SCL92: JP461.4, R186.1, U93.7
SCL93: JP466.4, R188.1, U94.7
SCL94: JP471.4, R190.1, U95.7
SCL95: JP476.4, R192.1, U96.7
SCL96: JP481.4, R194.1, U97.7
SCL97: JP486.4, R196.1, U98.7
SDA: JP1.3, R1.1, U1.6
SDA1: JP5.3, R3.1, U2.6
SDA2: JP11.3, R5.1, U3.6
SDA3: JP16.3, R7.1, U4.6
SDA4: JP21.3, R9.1, U5.6
SDA5: JP26.3, R11.1, U6.6
SDA6: JP31.3, R13.1, U7.6
SDA7: JP36.3, R15.1, U8.6
SDA8: JP41.3, R17.1, U9.6
SDA9: JP46.3, R19.1, U10.6
SDA10: JP51.3, R21.1, U11.6
SDA11: JP56.3, R23.1, U12.6
SDA12: JP61.3, R25.1, U13.6
SDA13: JP66.3, R27.1, U14.6
SDA14: JP71.3, R29.1, U15.6
SDA15: JP76.3, R31.1, U16.6
SDA16: JP81.3, R33.1, U17.6
SDA17: JP86.3, R35.1, U18.6
SDA18: JP91.3, R37.1, U19.6
SDA19: JP96.3, R39.1, U20.6
SDA20: JP101.3, R41.1, U21.6
SDA21: JP106.3, R43.1, U22.6
SDA22: JP111.3, R45.1, U23.6
SDA23: JP116.3, R47.1, U24.6
SDA24: JP121.3, R49.1, U25.6
SDA25: JP126.3, R51.1, U26.6
SDA26: JP131.3, R53.1, U27.6
SDA27: JP136.3, R55.1, U28.6
SDA28: JP141.3, R57.1, U29.6
SDA29: JP146.3, R59.1, U30.6
SDA30: JP151.3, R61.1, U31.6
SDA31: JP156.3, R63.1, U32.6
SDA32: JP161.3, R65.1, U33.6
SDA33: JP166.3, R67.1, U34.6
SDA34: JP171.3, R69.1, U35.6
SDA35: JP176.3, R71.1, U36.6
SDA36: JP181.3, R73.1, U37.6
SDA37: JP186.3, R75.1, U38.6
SDA38: JP191.3, R77.1, U39.6
SDA39: JP196.3, R79.1, U40.6
SDA40: JP201.3, R81.1, U41.6
SDA41: JP206.3, R83.1, U42.6
SDA42: JP211.3, R85.1, U43.6
SDA43: JP216.3, R87.1, U44.6
SDA44: JP221.3, R89.1, U45.6
SDA45: JP226.3, R91.1, U46.6
SDA46: JP231.3, R93.1, U47.6
SDA47: JP236.3, R95.1, U48.6
SDA48: JP241.3, R97.1, U49.6
SDA49: JP246.3, R99.1, U50.6
SDA50: JP251.3, R101.1, U51.6
SDA51: JP256.3, R103.1, U52.6
SDA52: JP261.3, R105.1, U53.6
SDA53: JP266.3, R107.1, U54.6
SDA54: JP271.3, R109.1, U55.6
SDA55: JP276.3, R111.1, U56.6
SDA56: JP281.3, R113.1, U57.6
SDA57: JP286.3, R115.1, U58.6
SDA58: JP291.3, R117.1, U59.6
SDA59: JP296.3, R119.1, U60.6
SDA60: JP301.3, R121.1, U61.6
SDA61: JP306.3, R123.1, U62.6
SDA62: JP311.3, R125.1, U63.6
SDA63: JP316.3, R127.1, U64.6
SDA64: JP321.3, R129.1, U65.6
SDA65: JP326.3, R131.1, U66.6
SDA66: JP331.3, R133.1, U67.6
SDA67: JP336.3, R135.1, U68.6
SDA68: JP341.3, R137.1, U69.6
SDA69: JP346.3, R139.1, U70.6
SDA70: JP351.3, R141.1, U71.6
SDA71: JP356.3, R143.1, U72.6
SDA72: JP361.3, R145.1, U73.6
SDA73: JP366.3, R147.1, U74.6
SDA74: JP371.3, R149.1, U75.6
SDA75: JP376.3, R151.1, U76.6
SDA76: JP381.3, R153.1, U77.6
SDA77: JP386.3, R155.1, U78.6
SDA78: JP391.3, R157.1, U79.6
SDA79: JP396.3, R159.1, U80.6
SDA80: JP401.3, R161.1, U81.6
SDA81: JP406.3, R163.1, U82.6
SDA82: JP411.3, R165.1, U83.6
SDA83: JP416.3, R167.1, U84.6
SDA84: JP421.3, R169.1, U85.6
SDA85: JP426.3, R171.1, U86.6
SDA86: JP431.3, R173.1, U87.6
SDA87: JP436.3, R175.1, U88.6
SDA88: JP441.3, R177.1, U89.6
SDA89: JP446.3, R179.1, U90.6
SDA90: JP451.3, R181.1, U91.6
SDA91: JP456.3, R183.1, U92.6
SDA92: JP461.3, R185.1, U93.6
SDA93: JP466.3, R187.1, U94.6
SDA94: JP471.3, R189.1, U95.6
SDA95: JP476.3, R191.1, U96.6
SDA96: JP481.3, R193.1, U97.6
SDA97: JP486.3, R195.1, U98.6
VCC: C3.1, C4.1, C5.1, JP1.2, SJ1.2, U1.2, U1.8
VCC1: C8.1, C9.1, C10.1, JP5.2, SJ2.2, U2.2, U2.8
VCC2: C13.1, C14.1, C15.1, JP11.2, SJ3.2, U3.2, U3.8
VCC3: C18.1, C19.1, C20.1, JP16.2, SJ4.2, U4.2, U4.8
VCC4: C23.1, C24.1, C25.1, JP21.2, SJ5.2, U5.2, U5.8
VCC5: C28.1, C29.1, C30.1, JP26.2, SJ6.2, U6.2, U6.8
VCC6: C33.1, C34.1, C35.1, JP31.2, SJ7.2, U7.2, U7.8
VCC7: C38.1, C39.1, C40.1, JP36.2, SJ8.2, U8.2, U8.8
VCC8: C43.1, C44.1, C45.1, JP41.2, SJ9.2, U9.2, U9.8
VCC9: C48.1, C49.1, C50.1, JP46.2, SJ10.2, U10.2, U10.8
VCC10: C53.1, C54.1, C55.1, JP51.2, SJ11.2, U11.2, U11.8
VCC11: C58.1, C59.1, C60.1, JP56.2, SJ12.2, U12.2, U12.8
VCC12: C63.1, C64.1, C65.1, JP61.2, SJ13.2, U13.2, U13.8
VCC13: C68.1, C69.1, C70.1, JP66.2, SJ14.2, U14.2, U14.8
VCC14: C73.1, C74.1, C75.1, JP71.2, SJ15.2, U15.2, U15.8
VCC15: C78.1, C79.1, C80.1, JP76.2, SJ16.2, U16.2, U16.8
VCC16: C83.1, C84.1, C85.1, JP81.2, SJ17.2, U17.2, U17.8
VCC17: C88.1, C89.1, C90.1, JP86.2, SJ18.2, U18.2, U18.8
VCC18: C93.1, C94.1, C95.1, JP91.2, SJ19.2, U19.2, U19.8
VCC19: C98.1, C99.1, C100.1, JP96.2, SJ20.2, U20.2, U20.8
VCC20: C103.1, C104.1, C105.1, JP101.2, SJ21.2, U21.2, U21.8
VCC21: C108.1, C109.1, C110.1, JP106.2, SJ22.2, U22.2, U22.8
VCC22: C113.1, C114.1, C115.1, JP111.2, SJ23.2, U23.2, U23.8
VCC23: C118.1, C119.1, C120.1, JP116.2, SJ24.2, U24.2, U24.8
VCC24: C123.1, C124.1, C125.1, JP121.2, SJ25.2, U25.2, U25.8
VCC25: C128.1, C129.1, C130.1, JP126.2, SJ26.2, U26.2, U26.8
VCC26: C133.1, C134.1, C135.1, JP131.2, SJ27.2, U27.2, U27.8
VCC27: C138.1, C139.1, C140.1, JP136.2, SJ28.2, U28.2, U28.8
VCC28: C143.1, C144.1, C145.1, JP141.2, SJ29.2, U29.2, U29.8
VCC29: C148.1, C149.1, C150.1, JP146.2, SJ30.2, U30.2, U30.8
VCC30: C153.1, C154.1, C155.1, JP151.2, SJ31.2, U31.2, U31.8
VCC31: C158.1, C159.1, C160.1, JP156.2, SJ32.2, U32.2, U32.8
VCC32: C163.1, C164.1, C165.1, JP161.2, SJ33.2, U33.2, U33.8
VCC33: C168.1, C169.1, C170.1, JP166.2, SJ34.2, U34.2, U34.8
VCC34: C173.1, C174.1, C175.1, JP171.2, SJ35.2, U35.2, U35.8
VCC35: C178.1, C179.1, C180.1, JP176.2, SJ36.2, U36.2, U36.8
VCC36: C183.1, C184.1, C185.1, JP181.2, SJ37.2, U37.2, U37.8
VCC37: C188.1, C189.1, C190.1, JP186.2, SJ38.2, U38.2, U38.8
VCC38: C193.1, C194.1, C195.1, JP191.2, SJ39.2, U39.2, U39.8
VCC39: C198.1, C199.1, C200.1, JP196.2, SJ40.2, U40.2, U40.8
VCC40: C203.1, C204.1, C205.1, JP201.2, SJ41.2, U41.2, U41.8
VCC41: C208.1, C209.1, C210.1, JP206.2, SJ42.2, U42.2, U42.8
VCC42: C213.1, C214.1, C215.1, JP211.2, SJ43.2, U43.2, U43.8
VCC43: C218.1, C219.1, C220.1, JP216.2, SJ44.2, U44.2, U44.8
VCC44: C223.1, C224.1, C225.1, JP221.2, SJ45.2, U45.2, U45.8
VCC45: C228.1, C229.1, C230.1, JP226.2, SJ46.2, U46.2, U46.8
VCC46: C233.1, C234.1, C235.1, JP231.2, SJ47.2, U47.2, U47.8
VCC47: C238.1, C239.1, C240.1, JP236.2, SJ48.2, U48.2, U48.8
VCC48: C243.1, C244.1, C245.1, JP241.2, SJ49.2, U49.2, U49.8
VCC49: C248.1, C249.1, C250.1, JP246.2, SJ50.2, U50.2, U50.8
VCC50: C253.1, C254.1, C255.1, JP251.2, SJ51.2, U51.2, U51.8
VCC51: C258.1, C259.1, C260.1, JP256.2, SJ52.2, U52.2, U52.8
VCC52: C263.1, C264.1, C265.1, JP261.2, SJ53.2, U53.2, U53.8
VCC53: C268.1, C269.1, C270.1, JP266.2, SJ54.2, U54.2, U54.8
VCC54: C273.1, C274.1, C275.1, JP271.2, SJ55.2, U55.2, U55.8
VCC55: C278.1, C279.1, C280.1, JP276.2, SJ56.2, U56.2, U56.8
VCC56: C283.1, C284.1, C285.1, JP281.2, SJ57.2, U57.2, U57.8
VCC57: C288.1, C289.1, C290.1, JP286.2, SJ58.2, U58.2, U58.8
VCC58: C293.1, C294.1, C295.1, JP291.2, SJ59.2, U59.2, U59.8
VCC59: C298.1, C299.1, C300.1, JP296.2, SJ60.2, U60.2, U60.8
VCC60: C303.1, C304.1, C305.1, JP301.2, SJ61.2, U61.2, U61.8
VCC61: C308.1, C309.1, C310.1, JP306.2, SJ62.2, U62.2, U62.8
VCC62: C313.1, C314.1, C315.1, JP311.2, SJ63.2, U63.2, U63.8
VCC63: C318.1, C319.1, C320.1, JP316.2, SJ64.2, U64.2, U64.8
VCC64: C323.1, C324.1, C325.1, JP321.2, SJ65.2, U65.2, U65.8
VCC65: C328.1, C329.1, C330.1, JP326.2, SJ66.2, U66.2, U66.8
VCC66: C333.1, C334.1, C335.1, JP331.2, SJ67.2, U67.2, U67.8
VCC67: C338.1, C339.1, C340.1, JP336.2, SJ68.2, U68.2, U68.8
VCC68: C343.1, C344.1, C345.1, JP341.2, SJ69.2, U69.2, U69.8
VCC69: C348.1, C349.1, C350.1, JP346.2, SJ70.2, U70.2, U70.8
VCC70: C353.1, C354.1, C355.1, JP351.2, SJ71.2, U71.2, U71.8
VCC71: C358.1, C359.1, C360.1, JP356.2, SJ72.2, U72.2, U72.8
VCC72: C363.1, C364.1, C365.1, JP361.2, SJ73.2, U73.2, U73.8
VCC73: C368.1, C369.1, C370.1, JP366.2, SJ74.2, U74.2, U74.8
VCC74: C373.1, C374.1, C375.1, JP371.2, SJ75.2, U75.2, U75.8
VCC75: C378.1, C379.1, C380.1, JP376.2, SJ76.2, U76.2, U76.8
VCC76: C383.1, C384.1, C385.1, JP381.2, SJ77.2, U77.2, U77.8
VCC77: C388.1, C389.1, C390.1, JP386.2, SJ78.2, U78.2, U78.8
VCC78: C393.1, C394.1, C395.1, JP391.2, SJ79.2, U79.2, U79.8
VCC79: C398.1, C399.1, C400.1, JP396.2, SJ80.2, U80.2, U80.8
VCC80: C403.1, C404.1, C405.1, JP401.2, SJ81.2, U81.2, U81.8
VCC81: C408.1, C409.1, C410.1, JP406.2, SJ82.2, U82.2, U82.8
VCC82: C413.1, C414.1, C415.1, JP411.2, SJ83.2, U83.2, U83.8
VCC83: C418.1, C419.1, C420.1, JP416.2, SJ84.2, U84.2, U84.8
VCC84: C423.1, C424.1, C425.1, JP421.2, SJ85.2, U85.2, U85.8
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
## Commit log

2013-12-04 Initial commit - v12
    Initial commit of hardware version 12. Changes from v11:
    1.) 0402 to 0603 footprints
    2.) Jumper selects for I2C pullup/pulldown
    3.) Traces all routed directly away from IC
    4.) tRestrict under IC for even reflow
    5.) OSHW and Creative Commons info
2013-12-04 generic readme template
    will update with complete info when product goes moves to production
2013-12-10 Fixed pullup jumper and C3 position
    Removed both three pad jumpers. Replaced with one jumper to pullup I2C
    lines. Moved C3 closer to pin 8. Corrected 4 way VCC net in schematic.
2013-12-11 Updated main IC to 1:1
    Updated footprint on main IC to 1:1 for better reflow and AOI.
2014-01-13 Modified I2C pullup solder jumper
    Changed solder jumper for I2C pullup so that I2C lines will be
    completely floating if jumper is open. Moved capacitor bank to the left
    .005 grid spaces and moved resistors and cap on right side over .005 to
    the right, all for better trace routing. Changed int trace to be more
    direct to header.
2014-02-24 Reordered Pinout
    1.) Reordered pinout to adhere to new I2C layout standard
    2.) Added "fake trace" to NC leg of IC for more uniform heat
    distribution.
    3.) Minor trace efficiency edits
2014-04-21 Silk updates
    1.) Added axis silk to bottom.
    2.) Added SFE flame to top silk.
    3.) Moved existing silk to accommodate additions.
2014-04-22 changed fiducials
2014-04-22 created panel v12
2015-03-10 Adding demo sketch and updating directory names
2015-03-10 file renamed by Arduino IDE
2015-03-10 change send -> write and receive -> read for updated Arduino environment
2015-03-10 reduce redundancy in read functions
2015-03-10 add prefix to function name
2015-03-10 further eliminate redundancy
2015-03-10 make function names more readable
2015-12-14 made larger panel
2016-10-25 Updating .git files, license, removing old firmware
2016-10-25 Squashed 'Libraries/Arduino/' content from commit e798e5d
    git-subtree-dir: Libraries/Arduino
    git-subtree-split: e798e5d01f4523ffde3f9dc01292ebfc96ab786e
2016-10-25 Updating readme with links, updated license info
2019-06-12 Removing old libraries. Adding links to formal libs in readme.
